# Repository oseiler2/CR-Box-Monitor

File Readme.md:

# Fan controller and CO2 Monitor for Corsi-Rosenthal boxes

An ESP32 based controller with integrated CO2 Monitor for PC-fans used in [Corsi-Rosenthal boxes](https://en.wikipedia.org/wiki/Corsi%E2%80%93Rosenthal_Box) and other diy air filters.

See [here](https://github.com/oseiler2/CO2Monitor) for some additional background on CO2 monitoring.

## Motivation

Many commercial air filters are expensive, under-dimensioned and noisy. Corsi-Rosenthal boxes are easy to make and very efficient air filters used to clean the air from airborne viral particles, allergens, smoke and other irritants.

The classic CR box design uses a box fan, which has some disadvantages:
- hard to get in some regions
- using mains voltage which can be a perceived or very real risk in some environments, e.g. classrooms
- can be noisy (depending on the fan)
- not easy to control

More recent designs have been replacing the box fan with an array of comparatively large, pressure optimised PC case fans, for example 9 x 140mm fans in a 3x3 grid on top of a 20 inch filter panel CR box. The smaller size of the fans also allows more flexibility in designing more portable CR boxes using 2 smaller filter panels.

Low speed PC fans are also much quieter and operate on safe 12V power.

By keeping the noise as low as possible and addressing the other above concerns the acceptance and tolerance of CR Boxes is increased. Commercial air cleaners are often turned off, or set to minimum levels, which contradicts their purpose. Further this controller and the operation of the fans and effectiveness can be monitored remotely.

[Learn more about this small CR box pictured below](https://github.com/oseiler2/HalfSizeCrBox)

# Sections

- [Features](#features) gives an overview of the capabilities and general operation
- [Hardware](#hardware) describes the board in more detail, which fans to use and how to connect them
- [PCBs](#pcbs) has more details on the design of the boards
- [Firmware](#firmware) describing the device's software features and how to use them
- [Cofiguration](#configuration) describing the device's software features and how to use them
- [Sensors](#sensors) has more information on the available sensors
- [Calibration](#calibration) has some important information on keeping the readings accurate

# Features

## General operation

The controller constantly assesses the air quality using the integrated CO2 monitor, air quality data via MQTT, or additional sensors connected via I2C, and regulates the fan speed accordingly. This will keep the airflow and related noise low while the air quality is generally good, either from good natural ventilation, or vacancy of the room. The integrated lights can reflect the air quality by showing a continuous spectrum from green via yellow to red and purple, or if configured just cycle through all colours. An integrated buzzer can also be used to alter on air quality threshold changes.

MQTT integration allows capturing all measured data and displaying on dashboards, as [documented here](https://github.com/oseiler2/CO2Monitor/blob/main/docker/docker.md).

## Key features

- Speed controller for 10 or more PC fans to regulate air flow depending on air quality
- compatible with 3 (no pwm) or 4 (pwm) pin. Non-pwm 3 pin fans are controlled using an integrated MosFET driven by a PWM signal
- 9 bright internal colour LEDs to indicate air quality with the option to connect more WS2812 (Neopixel) based LEDs
- integrated CO2, temperature and humidity sensor,
- alternatively capability to consume CO2 readings from another CO2 monitor via MQTT (eg [CO2Monitor](https://github.com/oseiler2/CO2Monitor))
- WiFi and MQTT enabled for reporting and/or consuming CO2 readings and remote configuration
- integrated buzzer to alert of poor air quality, or changes in air quality
- USB-PD compatibility to power everything off a USB-PD enabled power supply (phone charger)
- 12V direct input using 5.5x2.1mm Barrel Jack
- I2C connector to integrate other sensors
- SPS30 Particulate Matter sensor connector

# Firmware

## Firmware flashing

The firmware can be flashed onto the board directly from a supported browser [from here](https://oseiler2.github.io/CR-Box-Monitor/).

## Wifi

When not connected to a configured WiFi, the controller will automatically create an Access Point using the SSID CR-Box-<ESP32mac>. Connecting to this AP allows the Wifi credentials for the monitor to be set. The AP can also be forced by pressing the `Boot` button for less than 2 seconds.

The firmware also supports WiFi configuration using [Improv Wifi](https://www.improv-wifi.com/) when connected via USB to a computer and using a supported browser [from here](https://oseiler2.github.io/CR-Box-Monitor/).

A password for the AP can be configured in the file `extra.ini` which needs to be created by copying [extra.template.ini](extra.template.ini) and applying the desired changes.

## Configuration

The controller is configured via the `config.json file on the ESP32 file system. There are 3 ways the configuration can be changed:

- via the Web Interface
- by directly editing [config.json](data/config.json) and uploading it via `Upload Filesystem Image`
- via MQTT (once connected)

### Web Interface

Navigating a browser to the controller's IP address will open the Web Interface. Here you can select to Change the Wifi configuration, the more generic device configuration, look at logs or reboot the device.

The Web Interface can be protected by setting a username and password in the file `extra.ini` which needs to be created by copying [extra.template.ini](extra.template.ini) and applying the desired changes.

- `Device ID` unique id of the device, mainly used for MQTT
- `MQTT topic`, `MQTT username` , `MQTT password`, `MQTT host`, `MQTT port`, `MQTT TLS`, `MQTT ignore certificate errors` are all used to configure the MQTT host connection
- `Mirror other device's measurements` can be enabled to consume readings from another monitor using the `ID of device to mirror` and `MQTT topic of device to mirror` MQTT settings if the controller is not outfitted with a CO2 sensor
- `Altitude` is used to calibrate the SCD30/SCD4x CO2 sensor
- `CO2 Green threshold` sets the lower limit at which the fans will be set to idle speed. Any higher CO2 measurements increase the fan speed.
- `CO2 Yellow threshold`, `CO2 Red threshold`, `CO2 Dark threshold` set the limits for changing the LED colours and fan speed. The fan speed is continously increasing from the idle speed (green) to 50% (yellow) to full speed (red).
- `LED brightness PWM` sets the LED brightness on a scale from 0 to 255
- `Display colourwheel` changes the LEDs to circle throw all colours instead of reflecting air quality readings. This can be useful when no attention should be drawn to current CO2 levels.
- `Neopixel internal data pin` should be left at `17` and `Number of internal Neopixels` at `9` unless a different PCB configuration is being used.
- `Neopixel external data pin` should be set to `0` when no additional Neopixels are connected to the screw terminal, and set to `6` otherwise. `Number of external Neopixels` should be set to the number of additional Neopixels
- `Fans use 4 pin connector with PWM` needs to be enabled to control PWM enabled fans. If unticked the fan GND connection will be PWM driven to control 3-pin fans.
- `PWM when CO2 is low` sets the idle fan speed on a scale from 0 to 255. This should be set high enough that the fans do start up and keep spinning slowly, otherwise sufficient airflow cannot be guaranteed and the internal CO2 sensor might not give accurate readings.
- `Buzzer mode` configures the integrated buzzer to be always off, beep on every level change, or give a number of beeps depending on the CO2 level for each measurement.

### MQTT

Sensor readings can be published via MQTT for centralised storage and visualition. Each node is configured with its own id and will then publish under `crbox/<id>/up/sensors`. The top level topic `crbox` is configurable. Downlink messages to nodes can be sent to each individual node using the id in the topic `crbox/<id>/down/<command>`, or to all nodes when omitting the id part `crbox/down/<command>`

SCD3x/SCD4x

```
{
  "co2": 752,
  "temperature": "21.6",
  "humidity": "52.1",
  "fanPwm": 25
}
```

BME680

```
{
  "iaq": 19,
  "temperature": "19.2",
  "humidity": "75.6",
  "pressure": 1014
}
```

SPS30

```
{
  "pm0.5": 16,
  "pm1": 19,
  "pm2.5": 19,
  "pm4": 19,
  "pm10": 19
}
```

Sending `crbox/<id>/down/getConfig` will triger the node to reply with its current settings under `crbox/<id>/up/config`

```
{
  "appVersion": "1.0",
  "mac": "xxyyzz",
  "ip": "1.2.3.4",
  "scd40": true,
  "scd30": true,
  "bme680": true,
  "sps30": true,
  "sps30AutoCleanInt": 604800,
  "sps30Status": 0,
  "mqttTopic": "crbox",
  "mqttUsername": "crbox",
  "mqttHost": "1.2.3.4",
  "mqttServerPort": 1883,
  "mqttUseTls": true,
  "mqttInsecure": false,
  "mqttMirror": false,
  "mqttMirrordeviceId": 1,
  "mqttMirrorTopic": "co2monitor",
  "altitude": 5,
  "co2GreenThreshold": 450,
  "co2YellowThreshold": 700,
  "co2RedThreshold": 900,
  "co2DarkRedThreshold": 1200,
  "brightness": 255,
  "colourWheel": false,
  "neopixelIntData": 17,
  "neopixelIntNumber": 9,
  "neopixelExtData": 6,
  "neopixelExtNumber": 32,
  "fanHasPwm": true,
  "minPwm": 25,
  "buzzerMode": 0,
  "tempOffset": "4.0"
}
```

A message to `crbox/<id>/down/setConfig` will set the node's configuration to the provided parameters. Note that changes to the hardware configuration will trigger a reboot.

```
{
  "deviceId": 1,
  "mqttUsername": "crbox",
  "mqttPassword": "crbox",
  "mqttTopic": "crbox",
  "mqttUsername": "crbox",
  "mqttHost": "1.2.3.4",
  "mqttServerPort": 1883,
  "mqttUseTls": true,
  "mqttInsecure": false,
  "mqttMirror": false,
  "mqttMirrordeviceId": 1,
  "mqttMirrorTopic": "co2monitor",
  "altitude": 5,
  "co2GreenThreshold": 450,
  "co2YellowThreshold": 700,
  "co2RedThreshold": 900,
  "co2DarkRedThreshold": 1200,
  "brightness": 255,
  "colourWheel": false,
  "neopixelIntData": 17,
  "neopixelIntNumber": 9,
  "neopixelExtData": 6,
  "neopixelExtNumber": 32,
  "fanHasPwm": true,
  "minPwm": 25,
  "buzzerMode": 0,
  "tempOffset": "4.0"
}
```

A message to `crbox/<id>/down/setTemperatureOffset` will set the SCD3x/SCD4x's temperature offset (float, °C):

```
4.0
```

A message to `crbox/<id>/down/calibrate` will manually calibrate the SCD3x/SCD4x sensor to the given value:

```
412
```

A message to `crbox/<id>/down/setSPS30AutoCleanInterval` will set the SPS30 fan auto-clean interval in seconds to the given value:

```
604800
```

A message to `crbox/<id>/down/cleanSPS30` will run a fan clean on the SPS30.

A message to `crbox/<id>/down/installMqttRootCa` will attempt to install the pem-based ca cert in the payload as root cert for tls enabled MQTT connections. A connection attempt will be made using the configured MQTT settings and the new cert, and if successful the cert will be persisted, otherwise discarded.

A message to `crbox/<id>/down/installRootCa` will install the pem-based ca cert in the payload as root cert for OTA update requests.

A message to `crbox/<id>/down/ota` will trigger the OTA polling mechnism if configured.

A message to `crbox/<id>/down/forceota` will force an OTA update using the URL provided in the payload.

A message to `crbox/<id>/down/reboot` will trigger a reset on the node.

A message to `crbox/<id>/down/resetWifi` will wipe configured WiFi settings (SSID/password) and force a reboot.

### MQTT TLS support

To connect to an MQTT server using TLS (recommended) you need to enable TLS in the configuration by setting `mqttUseTls` to `true`. You also need to supply a root CA certificate in PEM format on the file system as `/mqtt_root_ca.pem` and/or a client certificate and key for using mTLS as `mqtt_client_cert.pem` and `mqtt_client_key.pem`. These files can be uploaded using the `Upload Filesystem Image` project task in PlatformIO. Alternatively you can set `mqttInsecure` to `true` to disable certificate validation altogether.

# Hardware

## Power

The board can be powered in 3 different ways:

1. Using a USB-PD capable power supply or phone charger, capable of delivering 12V and enough power (25W+). [charger - amazon.au](https://www.amazon.com.au/dp/B09NDG1MPP)
2. 12V direct input using 5.5x2.1mm Barrel Jack receptable
3. 12V screw terminal

Make sure to use a power supply that can deliver enough power. 140mm fans need about 150mA each. Each Neopixel can draw up to 60mA (540mA for all 9 integrated ones). The 5V DC-DC regulator is dimensioned for up to 2A - take that in mind when connecting additional Neopixels.

## Fans

Make sure to use pressure optimised low speed fans that are capable of delivering airflow at sufficient static pressure e.g. [Arctic P14](https://www.arctic.de/en/P14/ACFAN00136A) (2.4 mm H2O, 0.3 Sone, 123 m³/h) or [Arctic P12](https://www.arctic.de/en/P12/ACFAN00135A) (2.2 mm H20, 0.3 Sone, 95.7 m³/h).

The controller can read the RPM signal from the fan connected to the `Fan 1` connector

## Fan hub

The main board features up to 10 connectors for 3 or 4 pin fans. For builds where the fan cables are too short to reach to the main PCB, or when more than 10 fans should be connected, the fan hub PCB can be used to connect another 9 fans via an extension cable. To enale reading the RPM sigal connect the fan hub extension cable to the `Fan 1` connector on the main board and to the `Up` connector on the fan hub.

## Additional Neopixels

Additional [Neopixel strips](https://www.adafruit.com/category/183) can be connected using the dedicated screw terminal. Make sure to not overload the power supply and integrated 5V 2A linear regulator.

# PCBs

Main board [sources](pcb/CrBoxCo2Monitor%20V0.1/), [gerber files](pcb/CrBoxCo2Monitor%20V0.1/CrBoxCo2Monitor%20V0.1.zip) and [parts list](pcb/CrBoxCo2Monitor%20V0.1/bom.md).

Fan hub [sources](pcb/Fan%20hub%20v0.1/) and [gerber files](pcb/Fan%20hub%20v0.1/Fan%20hub%20v0.1.zip).

3d printable [board holder](stl/PCB%20holder.STL) using M3 threaded inserts

# Sensors

The presence of supported I2C based sensors/displays will be automatically detected on start-up.

## SCD3x

A SCD3x NDIR CO2 sensor can be connected to the designated footprint and will provide CO2, temperature and humidity readings via I2C. It supports a separate ready signal which is connected to the ESP32.

## SCD4x

A SCD4x NDIR CO2 sensor can be soldered directly onto the pcb and provides CO2, temperature and humidity readings via I2C.

## BME680

A BME680 sensor can be connected via the I2C JST header [Adafruit BME680](https://www.adafruit.com/product/3660), [STEMMA to JST SH Cable](https://www.adafruit.com/product/4424) to provide additional VOC and AIQ measurements.

## SPS30 Particulate matter sensor

The SPS30 sensor can be connected to the dedicated connector using a JST-ZR cable.

## other

Other I2C based sensors can be wired using the JST-PH I2C header.

# Calibration

CO2 sensors need to be regularly calibrated to provide reliable measurements. The used sensors support auto-calibration and that is enabled in the firmware. It works by looking over measurements over a period and calibrating the lowest value against 420ppm (configurable in the firmware). This is based on the assumption that the monitor 'sees' clean outside air about once a week. If that cannot be achieved the firmware also allows for a forced calibration against a given value. Please also make sure to set the altitude setting according to the monitor location. For details please check the sensor's datasheets.

Manual calibration can be triggered by pressing the `Boot` button for more than 5 seconds. Make sure the monitor has been exposed to fresh outside air for a while and be careful not to breathe towards the monitor when doing this.

Calibration can also be triggered remotely via [MQTT](#mqtt).

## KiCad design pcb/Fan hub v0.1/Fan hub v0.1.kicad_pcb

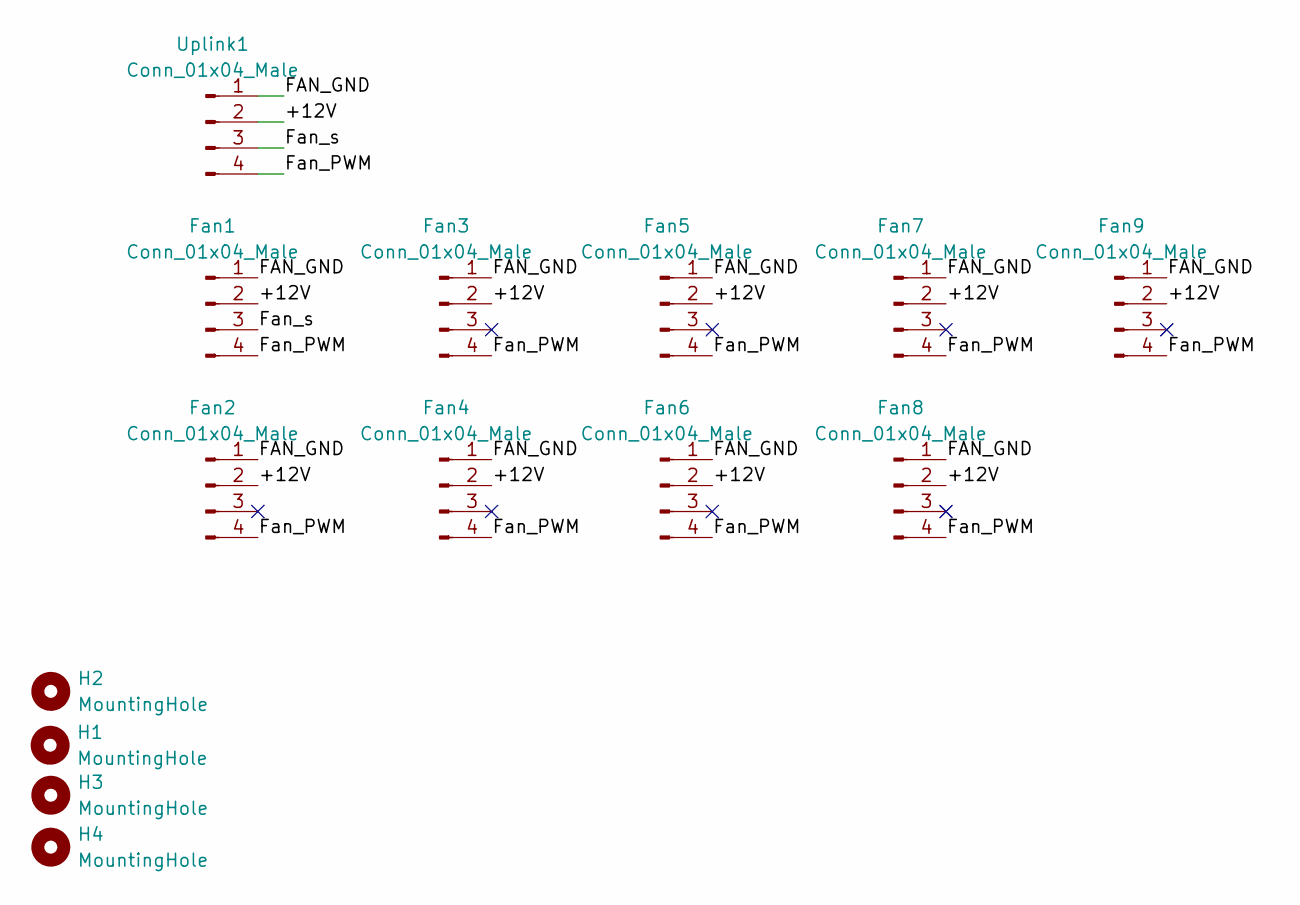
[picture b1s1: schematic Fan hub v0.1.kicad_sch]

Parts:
Fan1, Fan2, Fan3, Fan4, Fan5, Fan6, Fan7, Fan8, Fan9: Conn_01x04_Male; Molex_KK-254_AE-6410-04A_1x04_P2.54mm_Vertical
H1, H2, H3, H4: MountingHole; MountingHole_3.5mm
Uplink1: Conn_01x04_Male; Molex_KK-254_AE-6410-04A_1x04_P2.54mm_Vertical

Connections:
/+12V: Fan1.2, Fan2.2, Fan3.2, Fan4.2, Fan5.2, Fan6.2, Fan7.2, Fan8.2, Fan9.2, Uplink1.2
/FAN_GND: Fan1.1, Fan2.1, Fan3.1, Fan4.1, Fan5.1, Fan6.1, Fan7.1, Fan8.1, Fan9.1, Uplink1.1
/Fan_PWM: Fan1.4, Fan2.4, Fan3.4, Fan4.4, Fan5.4, Fan6.4, Fan7.4, Fan8.4, Fan9.4, Uplink1.4
/Fan_s: Fan1.3, Uplink1.3

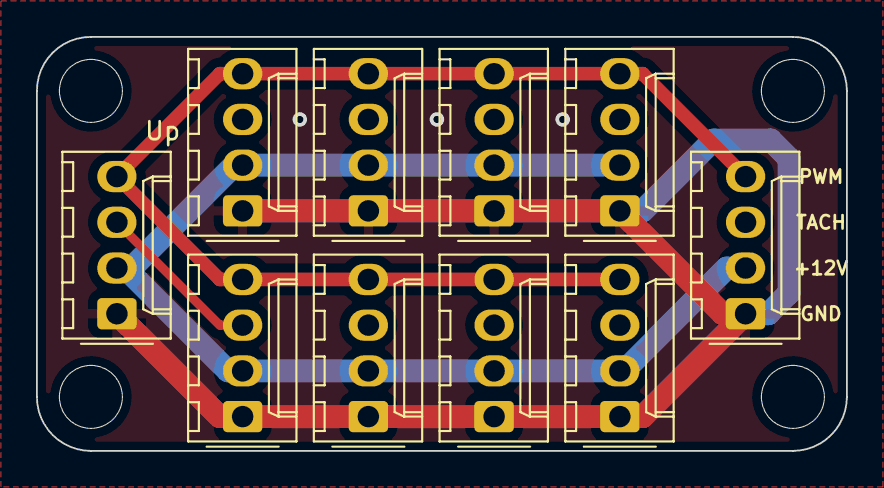
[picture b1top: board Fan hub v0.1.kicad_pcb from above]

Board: 2 copper layers, 45.0 x 23.0 mm, 14 parts (0 on the bottom side), 4 nets.

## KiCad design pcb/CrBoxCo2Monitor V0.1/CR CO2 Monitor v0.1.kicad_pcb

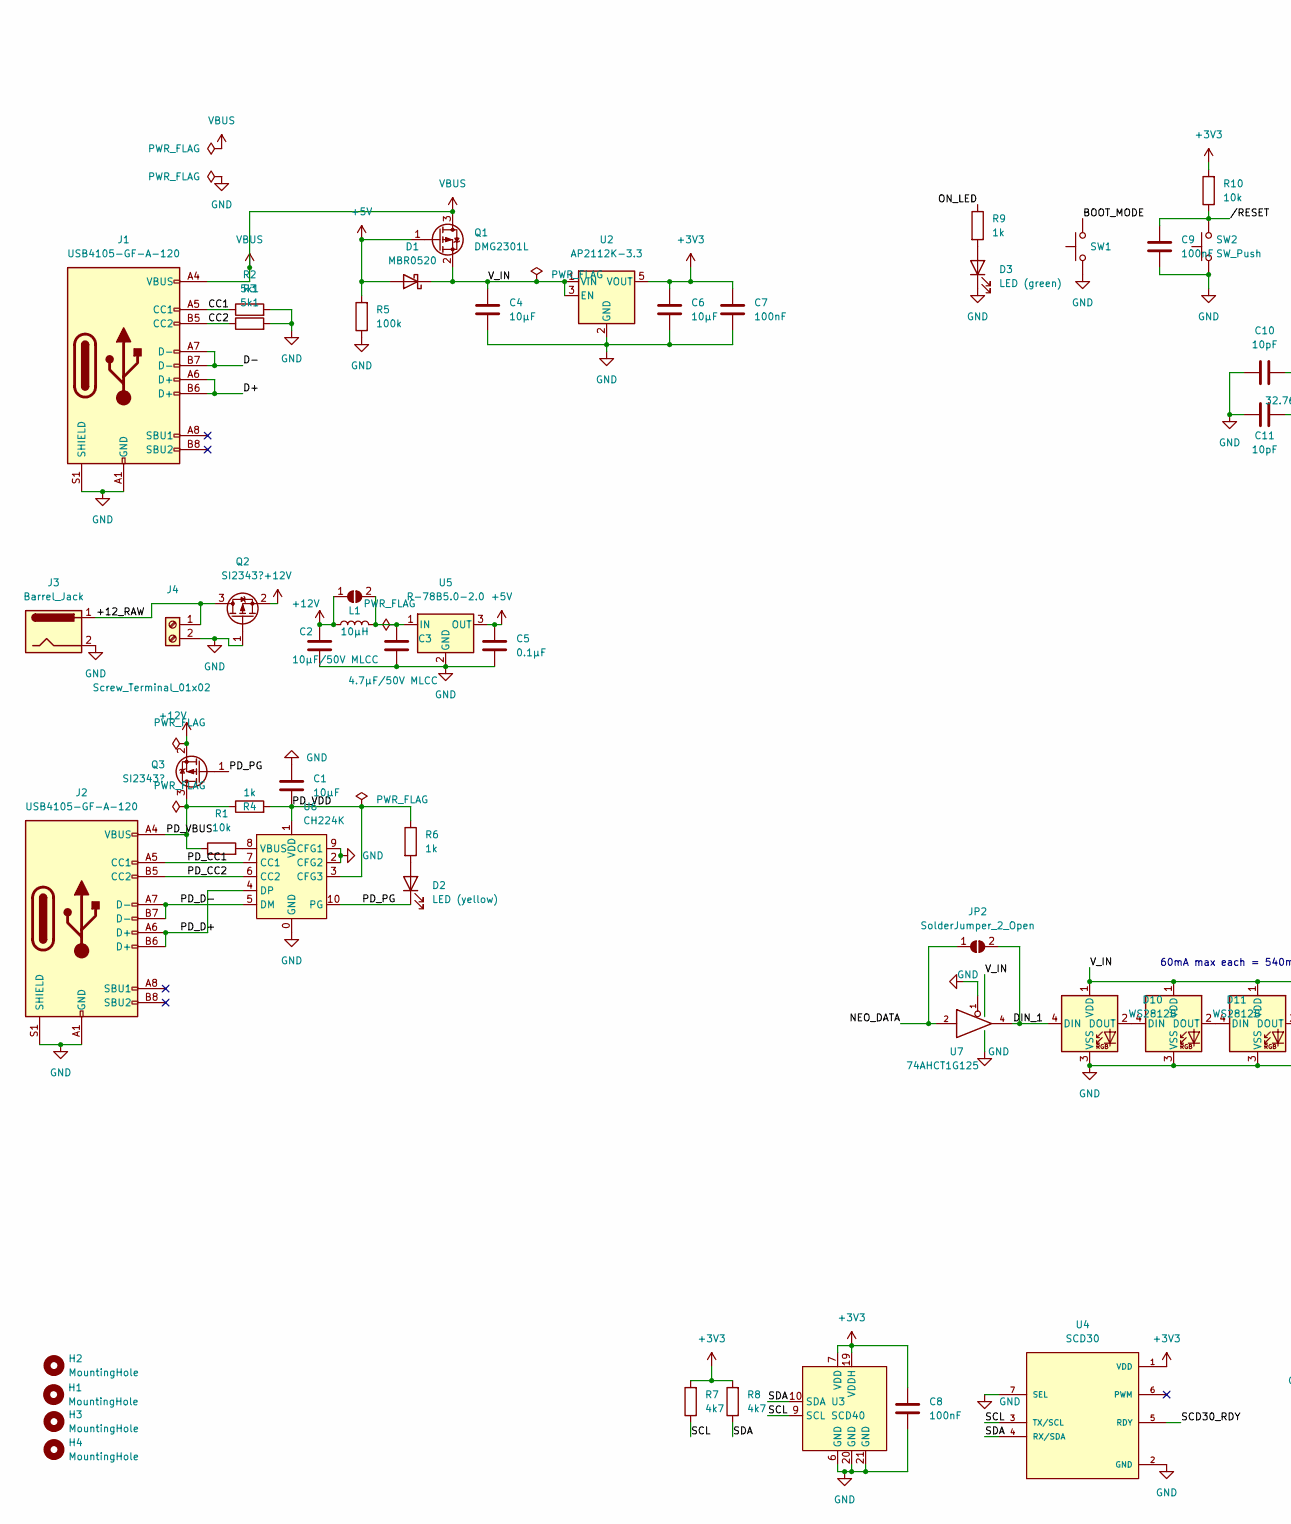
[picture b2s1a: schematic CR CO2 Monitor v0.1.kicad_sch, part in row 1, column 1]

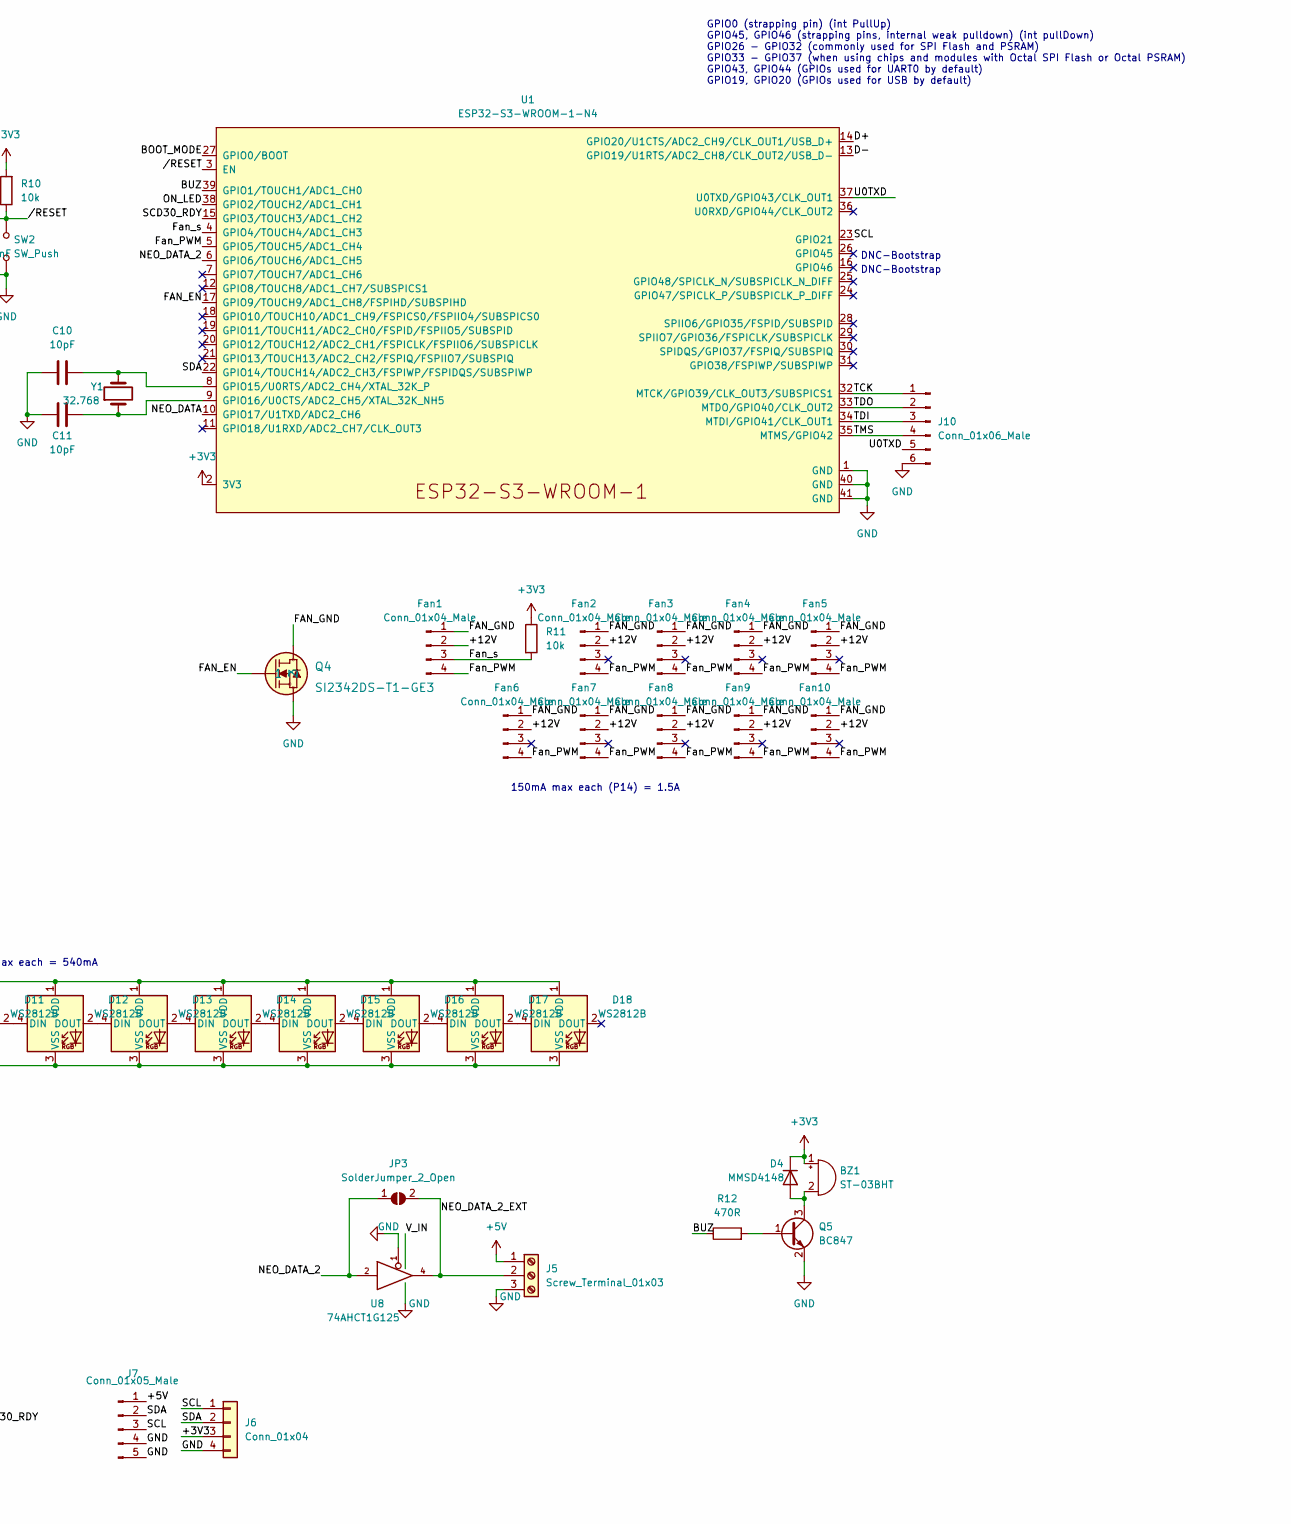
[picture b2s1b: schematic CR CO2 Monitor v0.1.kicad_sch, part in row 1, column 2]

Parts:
BZ1: ST-03BHT; XDCR_SMT-0827-S-HT-R
C1, C4, C6: 10μF; C_0805_2012Metric
C2: 10μF/50V MLCC; C_1210_3225Metric
C3: 4.7μF/50V MLCC; C_1210_3225Metric
C5: 0.1μF; C_0603_1608Metric
C7, C8, C9: 100nF; C_0603_1608Metric
C10, C11: 10pF; C_0603_1608Metric
D1: MBR0520; D_SOD-123
D2: LED (yellow); LED_0805_2012Metric
D3: LED (green); LED_0805_2012Metric
D4: MMSD4148; D_SOD-123
D10, D11, D12, D13, D14, D15, D16, D17, D18: WS2812B; LED_WS2812B_PLCC4_5.0x5.0mm_P3.2mm
Fan1, Fan2, Fan3, Fan4, Fan5, Fan6, Fan7, Fan8, Fan9, Fan10: Conn_01x04_Male; Molex_KK-254_AE-6410-04A_1x04_P2.54mm_Vertical
H1, H2, H3, H4: MountingHole; MountingHole_3.5mm
J1, J2: USB4105-GF-A-120; USB_C_Receptacle_XKB_U262-16XN-4BVC11; JLCPCB TYPE-C-31-M-12
J3: Barrel_Jack; BarrelJack_Horizontal
J4: Screw_Terminal_01x02; TerminalBlock_Phoenix_MKDS-1,5-2-5.08_1x02_P5.08mm_Horizont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
J5: Screw_Terminal_01x03; TerminalBlock_Phoenix_MKDS-1,5-3-5.08_1x03_P5.08mm_Horizont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
J6: Conn_01x04; JST_PH_B4B-PH-K_1x04_P2.00mm_Vertical
J7: Conn_01x05_Male; JST_B5B-ZR(LF)(SN)
J10: Conn_01x06_Male; PinHeader_1x06_P2.54mm_Vertical
JP1, JP2, JP3: SolderJumper_2_Open; SolderJumper-2_P1.3mm_Open_TrianglePad1.0x1.5mm
L1: 10μH; L_Taiyo-Yuden_NR-60xx
Q1: DMG2301L; SOT-23
Q2, Q3: SI2343?; SOT-23
Q4: SI2342DS-T1-GE3; TSOT-23
Q5: BC847; SOT-23
R1, R10, R11: 10k; R_0603_1608Metric
R2, R3: 5k1; R_0603_1608Metric
R4, R6, R9: 1k; R_0603_1608Metric
R5: 100k; R_0603_1608Metric
R7, R8: 4k7; R_0603_1608Metric
R12: 470R; R_0603_1608Metric
SW1, SW2: SW_Push; SW_Push_1P1T_NO_CK_KMR2
U1: ESP32-S3-WROOM-1-N4; ESP32-S3-WROOM-1
U2: AP2112K-3.3; SOT-23-5
U3: SCD40; SCD40-D-R1
U4: SCD30; PARTREV D1
U5: R-78B5.0-2.0; Converter_DCDC_RECOM_R-78B-2.0_THT
U6: CH224K; CH224K-ESSOP-10
U7, U8: 74AHCT1G125; SOT-23-5
Y1: 32.768; Crystal_SMD_3215-2Pin_3.2x1.5mm; Digikey CM7VT1A32.768KHZ125PF20PPMTBQAT3

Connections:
+3V3: BZ1.1 (-), C6.1, C7.1, C8.1, D4.1 (K), J6.3, R7.2, R8.2, R10.2, R11.1, U1.2 (3V3), U2.5 (VOUT), U3.7 (VDD), U3.19 (VDDH), U4.1 (VDD)
+5V: C5.1, D1.2 (A), J5.1, J7.1, Q1.1 (G), R5.2, U5.3 (OUT)
+12V: C2.1, Fan1.2, Fan2.2, Fan3.2, Fan4.2, Fan5.2, Fan6.2, Fan7.2, Fan8.2, Fan9.2, Fan10.2, JP1.1 (A), L1.1, Q2.2 (S), Q3.2 (S)
/+12_RAW: J3.1, J4.1, Q2.3 (D)
/BOOT_MODE: SW1.2, U1.27 (GPIO0/BOOT)
/BUZ: R12.1, U1.39 (GPIO1/TOUCH1/ADC1_CH0)
/CC1: J1.A5 (CC1), R2.1
/CC2: J1.B5 (CC2), R3.1
/D+: J1.A6 (D+), J1.B6 (D+), U1.14 (GPIO20/U1CTS/ADC2_CH9/CLK_OUT1/USB_D+)
/D-: J1.A7 (D-), J1.B7 (D-), U1.13 (GPIO19/U1RTS/ADC2_CH8/CLK_OUT2/USB_D-)
/DIN_1: D10.4 (DIN), JP2.2 (B), U7.4
/FAN_EN: Q4.1, U1.17 (GPIO9/TOUCH9/ADC1_CH8/FSPIHD/SUBSPIHD)
/FAN_GND: Fan1.1, Fan2.1, Fan3.1, Fan4.1, Fan5.1, Fan6.1, Fan7.1, Fan8.1, Fan9.1, Fan10.1, Q4.3
/Fan_PWM: Fan1.4, Fan2.4, Fan3.4, Fan4.4, Fan5.4, Fan6.4, Fan7.4, Fan8.4, Fan9.4, Fan10.4, U1.5 (GPIO5/TOUCH5/ADC1_CH4)
/Fan_s: Fan1.3, R11.2, U1.4 (GPIO4/TOUCH4/ADC1_CH3)
/NEO_DATA: JP2.1 (A), U1.10 (GPIO17/U1TXD/ADC2_CH6), U7.2
/NEO_DATA_2: JP3.1 (A), U1.6 (GPIO6/TOUCH6/ADC1_CH5), U8.2
/NEO_DATA_2_EXT: J5.2, JP3.2 (B), U8.4
/ON_LED: R9.1, U1.38 (GPIO2/TOUCH2/ADC1_CH1)
/PD_CC1: J2.A5 (CC1), U6.7 (CC1)
/PD_CC2: J2.B5 (CC2), U6.6 (CC2)
/PD_D+: J2.A6 (D+), J2.B6 (D+), U6.4 (DP)
/PD_D-: J2.A7 (D-), J2.B7 (D-), U6.5 (DM)
/PD_PG: D2.1 (K), Q3.1 (G), U6.10 (PG)
/PD_VBUS: J2.A4 (VBUS), J2.A9 (VBUS), J2.B4 (VBUS), J2.B9 (VBUS), Q3.3 (D), R1.1, R4.1
/PD_VDD: C1.2, R4.2, R6.1, U6.1 (VDD), U6.3 (CFG3)
/SCD30_RDY: U1.15 (GPIO3/TOUCH3/ADC1_CH2), U4.5 (RDY)
/SCL: J6.1, J7.3, R7.1, U1.23 (GPIO21), U3.9 (SCL), U4.3 (TX/SCL)
/SDA: J6.2, J7.2, R8.1, U1.22 (GPIO14/TOUCH14/ADC2_CH3/FSPIWP/FSPIDQS/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), U3.10 (SDA), U4.4 (RX/SDA)
/TCK: J10.1, U1.32 (MTCK/GPIO39/CLK_OUT3/SUBSPICS1)
/TDI: J10.3, U1.34 (MTDI/GPIO41/CLK_OUT1)
/TDO: J10.2, U1.33 (MTDO/GPIO40/CLK_OUT2)
/TMS: J10.4, U1.35 (MTMS/GPIO42)
/U0TXD: J10.5, U1.37 (U0TXD/GPIO43/CLK_OUT1)
//RESET: C9.1, R10.1, SW2.2, U1.3 (EN)
GND: C1.1, C2.2, C3.2, C4.2, C5.2, C6.2, C7.2, C8.2, C9.2, C10.1, C11.1, D3.1 (K), D10.3 (VSS), D11.3 (VSS), D12.3 (VSS), D13.3 (VSS), D14.3 (VSS), D15.3 (VSS), D16.3 (VSS), D17.3 (VSS), D18.3 (VSS), J1.A1 (GND), J1.A12 (GND), J1.B1 (GND), J1.B12 (GND), J1.S1 (SHIELD), J2.A1 (GND), J2.A12 (GND), J2.B1 (GND), J2.B12 (GND), J2.S1 (SHIELD), J3.2, J4.2, J5.3, J6.4, J7.4, J7.5, J10.6, Q2.1 (G), Q4.2, Q5.2 (E), R2.2, R3.2, R5.1, SW1.1, SW2.1, U1.1 (GND), U1.40 (GND), U1.41 (GND), U2.2 (GND), U3.6 (GND), U3.20 (GND), U3.21 (GND), U4.2 (GND), U4.7 (SEL), U5.2 (GND), U6.0 (GND), U6.2 (CFG2), U6.9 (CFG1), U7.1, U7.3 (GND), U8.1, U8.3 (GND)
unnamed: BZ1.2 (+), D4.2 (A), Q5.3 (C)
unnamed: C3.1, JP1.2 (B), L1.2, U5.1 (IN)
unnamed: C10.2, U1.8 (GPIO15/U0RTS/ADC2_CH4/XTAL_32K_P), Y1.2
unnamed: C11.2, U1.9 (GPIO16/U0CTS/ADC2_CH5/XTAL_32K_NH5), Y1.1
unnamed: D2.2 (A), R6.2
unnamed: D3.2 (A), R9.2
unnamed: D10.2 (DOUT), D11.4 (DIN)
unnamed: D11.2 (DOUT), D12.4 (DIN)
unnamed: D12.2 (DOUT), D13.4 (DIN)
unnamed: D13.2 (DOUT), D14.4 (DIN)
unnamed: D14.2 (DOUT), D15.4 (DIN)
unnamed: D15.2 (DOUT), D16.4 (DIN)
unnamed: D16.2 (DOUT), D17.4 (DIN)
unnamed: D17.2 (DOUT), D18.4 (DIN)
unnamed: Q5.1 (B), R12.2
unnamed: R1.2, U6.8 (VBUS)
VBUS: J1.A4 (VBUS), J1.A9 (VBUS), J1.B4 (VBUS), J1.B9 (VBUS), Q1.3 (D)
VCC: C4.1, D1.1 (K), D10.1 (VDD), D11.1 (VDD), D12.1 (VDD), D13.1 (VDD), D14.1 (VDD), D15.1 (VDD), D16.1 (VDD), D17.1 (VDD), D18.1 (VDD), Q1.2 (S), U2.1 (VIN), U2.3 (EN), U7.5 (VCC), U8.5 (VCC)

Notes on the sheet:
DNC-Bootstrap
60mA max each = 540mA
GPIO0 (strapping pin) (int PullUp) GPIO45, GPIO46 (strapping pins, internal weak pulldown) (int pullDown) GPIO26 - GPIO32 (commonly used for SPI Flash and PSRAM) GPIO33 - GPIO37 (when using chips and modules with Octal SPI Flash or Octal PSRAM) GPIO43, GPIO44 (GPIOs used for UART0 by default) GPIO1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
150mA max each (P14) = 1.5A

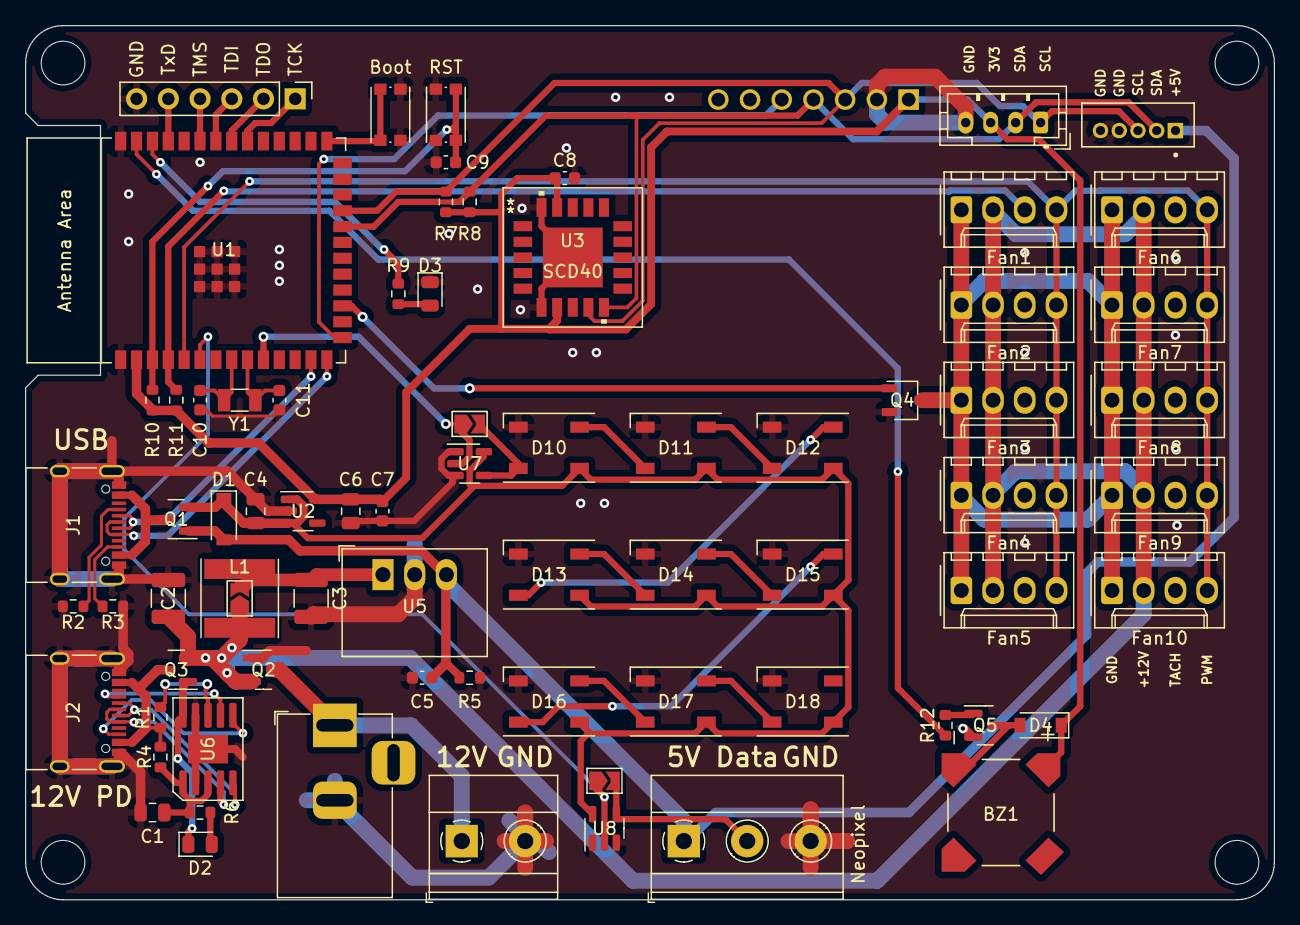
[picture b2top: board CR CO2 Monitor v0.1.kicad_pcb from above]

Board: 2 copper layers, 100.0 x 70.0 mm, 79 parts (1 on the bottom side), 54 nets.

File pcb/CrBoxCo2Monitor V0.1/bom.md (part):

# BOM

Note: the components marked in the 'Function' column are optional and only needed for the mentioned function.
For example if you want the second USB port to power the PCB with 12V via a USB-C PD power supply you need to populate all components marked with USB-PD.

| Quantity | Designator                                                  | Description                 | Function (optional) | Footprint | Part #              | Supplier                                                                                                  | Alternative                                                                                                     |
| -------- | ----------------------------------------------------------- | --------------------------- | ------------------- | --------- | ------------------- | --------------------------------------------------------------------------------------------------------- | --------------------------------------------------------------------------------------------------------------- |
| 1        | BZ1                                                         | Buzzer                      | Buzzer              |           | ST-03BHT            | [DigiKey](https://www.digikey.com/en/products/detail/soberton-inc/ST-0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                      |                                                                                                                 |
| 1        | C1                                                          | 10μF                        | USB-PD              | 0603      |                     |                                                                                                           |                                                                                                                 |
| 2        | C4, C6                                                      | 10μF                        |                     | 0603      |                     |                                                                                                           |                                                                                                                 |
| 1        | C2                                                          | 10μF/50V MLCC               |                     | 1210      | CL32B106KBJNNNE     | [DigiKey](https://www.digikey.co.nz/en/products/detail/samsung-electro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 |                                                                                                                 |
| 1        | C3                                                          | 4.7μF/50V MLCC              |                     | 1210      | CL32B475KBUYNNE     | [DigiKey](https://www.digikey.co.nz/en/products/detail/samsung-electro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 |                                                                                                                 |
| 4        | C5, C7, C8, C9                                              | 100nF                       |                     | 0603      |                     |                                                                                                           |                                                                                                                 |
| 1        | D1                                                          | Schottky diode 20V 500MA    |                     | SOD-123   | MBR0520             | [DigiKey](https://www.digikey.co.nz/en/products/detail/micro-commercia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             |                                                                                                                 |
| 1        | D2                                                          | LED yellow 2mA 2.1V         | USB-PD              | 0805      | KPT-2012YC          | [Element14](https://nz.element14.com/kingbright/kpt-2012yc/led-0805-yell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         |                                                                                                                 |
| 1        | D3                                                          | LED green 2mA 2.65V         |                     | 0805      | KPT-2012LVZGCK      | [Element14](https://nz.element14.com/kingbright/kpt-2012lvzgck/led-green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      |                                                                                                                 |
| 1        | D4                                                          | 200mA general purpose diode | Buzzer              | SOD-123   | MMSD4148            | [DigiKey](https://www.digikey.co.nz/en/products/detail/onsemi/MMSD4148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                           |                                                                                                                 |
| 9        | D10, D11, D12, D13, D14, D15, D16, D17, D18                 | WS2812B                     |                     | 5050      |                     | [AliExpress](https://www.aliexpress.com/item/1005002653014067.html)                                       |                                                                                                                 |
| 1-10     | Fan1, Fan2, Fan3, Fan4, Fan5, Fan6, Fan7, Fan8, Fan9, Fan10 | 3/4 pin Molex_KK-254        |                     |           |                     | [AliExpress](https://www.aliexpress.com/item/32961935772.html)                                            | [DigiKey](https://www.digikey.com/en/products/detail/sullins-connector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 |
| 1        | J1                                                          | USB4105-GF-A-120            |                     |           |                     | [DigiKey](https://www.digikey.com/en/products/detail/gct/USB4105-GF-A-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                       |                                                                                                                 |
| 1        | J2                                                          | USB4105-GF-A-120            | USB-PD              |           |                     | [DigiKey](https://www.digikey.com/en/products/detail/gct/USB4105-GF-A-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                       |                                                                                                                 |
| 1        | J3                                                          | Barrel Jack 5.5x2.1mm       | 12V in DC-Barrel    |           |                     | [DigiKey](https://www.digikey.com/en/products/detail/tensility-interna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      |                                                                                                                 |
| 1        | J4                                                          | Screw_Terminal_01x02 5.08   |                     |           |                     | [DigiKey](https://www.digikey.com/en/products/detail/te-connectivity-a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    |                                                                                                                 |
| 1        | J5                                                          | Screw_Terminal_01x03 5.08   |                     |           |                     | [DigiKey](https://www.digikey.com/en/products/detail/te-connectivity-a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     |                                                                                                                 |
| 1        | J6                                                          | JST_PH_B4B-PH-K             | optional I2C        |           |                     | [DigiKey](https://www.digikey.com/en/products/detail/jst-sales-america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       |                                                                                                                 |
| 1        | J7                                                          | JST_B5B-ZR                  | optional SPS30 PM   |           |                     | [DigiKey](https://www.digikey.com/en/products/detail/jst-sales-america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           |                                                                                                                 |
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
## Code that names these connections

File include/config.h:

#ifndef _CONFIG_H
#define _CONFIG_H

#include <logging.h>
#include <sdkconfig.h>

#define OTA_URL               "https://otahost/crbox/firmware.json"
#define OTA_APP               "crbox"
//#define OTA_POLL


#if CONFIG_IDF_TARGET_ESP32

#define LED_PIN                2
#define BUZZER_PIN             4
#define BTN_1                  0
#define NEO_DATA_INT          16
#define NEO_DATA_EXT          17
#define FAN_HALL              25
#define FAN_PWM               26
#define FAN_EN                27
#define SDA_PIN              SDA
#define SCL_PIN              SCL
#define SCD30_RDY_PIN         35

#elif CONFIG_IDF_TARGET_ESP32S3

#define LED_PIN                2
#define BUZZER_PIN             1
#define BTN_1                  0
#define NEO_DATA_INT          17
#define NEO_DATA_EXT           6
#define XTAL_32k_1            15
#define XTAL_32k_2            16
#define FAN_HALL               4
#define FAN_PWM                5
#define FAN_EN                 9
#define SDA_PIN               14
#define SCL_PIN               21
#define SCD30_RDY_PIN          3

#endif

#define I2C_CLK 100000UL
#define SCD30_I2C_CLK 50000UL   // SCD30 recommendation of 50kHz

static const char* CONFIG_FILENAME = "/config.json";
static const char* MQTT_ROOT_CA_FILENAME = "/mqtt_root_ca.pem";
static const char* MQTT_CLIENT_CERT_FILENAME = "/mqtt_client_cert.pem";
static const char* MQTT_CLIENT_KEY_FILENAME = "/mqtt_client_key.pem";
static const char* TEMP_MQTT_ROOT_CA_FILENAME = "/temp_mqtt_root_ca.pem";
static const char* ROOT_CA_FILENAME = "/root_ca.pem";

#define MQTT_QUEUE_LENGTH      25

#define PWM_CHANNEL_FAN         0
#define PWM_CHANNEL_BUZZER      2

// ----------------------------  Config struct ------------------------------------- 
#define CONFIG_SIZE 1280

#define MQTT_USERNAME_LEN 20
#define MQTT_PASSWORD_LEN 20
#define MQTT_HOSTNAME_LEN 30
#define MQTT_TOPIC_LEN 30
#define SSID_LEN 32
#define WIFI_PASSWORD_LEN 64

typedef enum : uint8_t {
  BUZ_OFF = 0,
  BUZ_LVL_CHANGE,
  BUZ_ALWAYS
} BuzzerMode;

struct Config {
  uint16_t deviceId;
  char mqttTopic[MQTT_TOPIC_LEN + 1];
  char mqttUsername[MQTT_USERNAME_LEN + 1];
  char mqttPassword[MQTT_PASSWORD_LEN + 1];
  char mqttHost[MQTT_HOSTNAME_LEN + 1];
  bool mqttUseTls;
  bool mqttInsecure;
  bool mqttMirrorDevice;
  uint16_t mqttMirrordeviceId;
  char mqttMirrorTopic[MQTT_TOPIC_LEN + 1];
  uint16_t mqttServerPort;
  uint16_t altitude;
  uint16_t co2GreenThreshold;
  uint16_t co2YellowThreshold;
  uint16_t co2RedThreshold;
  uint16_t co2DarkRedThreshold;
  uint8_t brightness;
  bool colourWheel;
  uint8_t neopixelIntData;
  uint8_t neopixelIntNumber;
  uint8_t neopixelExtData;
  uint8_t neopixelExtNumber;
  uint8_t minPwm;
  uint8_t buzzerPin = BUZZER_PIN;
  bool fanHasPwm;
  BuzzerMode buzzerMode = BUZ_LVL_CHANGE;
};

#endif

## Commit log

2023-06-23 docs
2023-06-23 fix url
2023-06-23 Deploying to docs from @ oseiler2/CR-Box-Monitor@1e10eaca1815af82a47ca0d6f9cfe555e51b0f24 🚀
2023-07-13 fix initial wifi state
2023-07-13 Deploying to docs from @ oseiler2/CR-Box-Monitor@ea7b67c5204e62624b202b0e996cdee7402c3a9b 🚀
2023-07-13 PCBs and BOM
2023-07-13 Deploying to docs from @ oseiler2/CR-Box-Monitor@d085b4254982343cdea388b47183335c3d94bde2 🚀
2023-07-14 Correct footprint
2023-07-14 Deploying to docs from @ oseiler2/CR-Box-Monitor@d93156a15ac8fda4328d08d077d0a69020168671 🚀
2023-07-16 Add fan pwm to MQTT data
2023-07-16 Deploying to docs from @ oseiler2/CR-Box-Monitor@72db40015fe780f835f24ccd3527159ac3259555 🚀
2023-07-18 Change fan PWM frequency to 40kHz
2023-07-18 Deploying to docs from @ oseiler2/CR-Box-Monitor@81f2e6d7b61ae71f678df6e9c68f8f4a27f1e64c 🚀
2023-07-22 Documentation
2023-07-22 Deploying to docs from @ oseiler2/CR-Box-Monitor@b83449350294325668839e7d381e6b548afaf9c9 🚀
